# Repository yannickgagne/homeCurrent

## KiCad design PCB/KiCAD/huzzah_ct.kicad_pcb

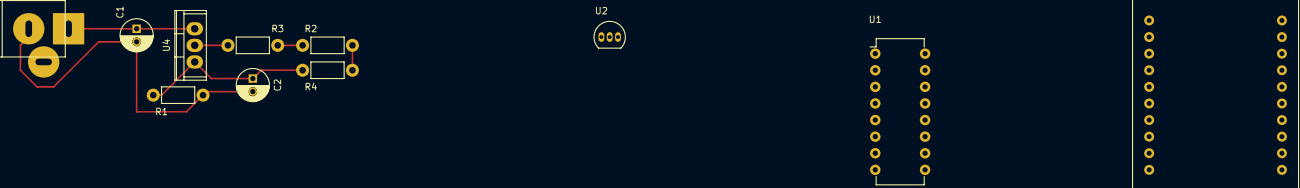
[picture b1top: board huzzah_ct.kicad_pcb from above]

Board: 2 copper layers, 11 parts (0 on the bottom side), 6 nets.

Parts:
C1: 0.1uF; C_Radial_D5_L11_P2
C2: 10uF; C_Radial_D5_L11_P2
CON1: BARREL_JACK; JACK_ALIM
R1, R2, R3, R4: 150; Resistor_Horizontal_RM7mm
U1: MCP3008; DIP-16_W7.62mm
U2: DS18B20; TO-92_Inline_Narrow_Oval
U3: Adafruit_HUZZAH; Adafruit HUZZAH
U4: LM317T; TO-220

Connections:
GNDREF: C1.2, C2.2, CON1.2, R1.2
unnamed: C1.1, CON1.1, U4.3
unnamed: C2.1, R1.1, R4.1, U4.1
unnamed: R2.1, R4.2
unnamed: R2.2, R3.1
unnamed: R3.2, U4.2

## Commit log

2016-03-06 main sketch
2016-03-07 Base
    Switch to PlatformIO IDE and structure.
2016-03-07 Cleanup
    Made some functions to make code more readable.
2016-03-08 Small tweaks
2016-03-09 send to TS at each 60s
2016-03-09 pcb stuff
2016-03-11 pcb work
2016-03-14 PCB stuff again
2016-03-14 move readme
2016-03-14 not much
2016-03-14 pcb routing
2016-03-15 hide config
2016-03-15 removed some secrets
2016-03-26 filenames
2016-03-30 structure changes
